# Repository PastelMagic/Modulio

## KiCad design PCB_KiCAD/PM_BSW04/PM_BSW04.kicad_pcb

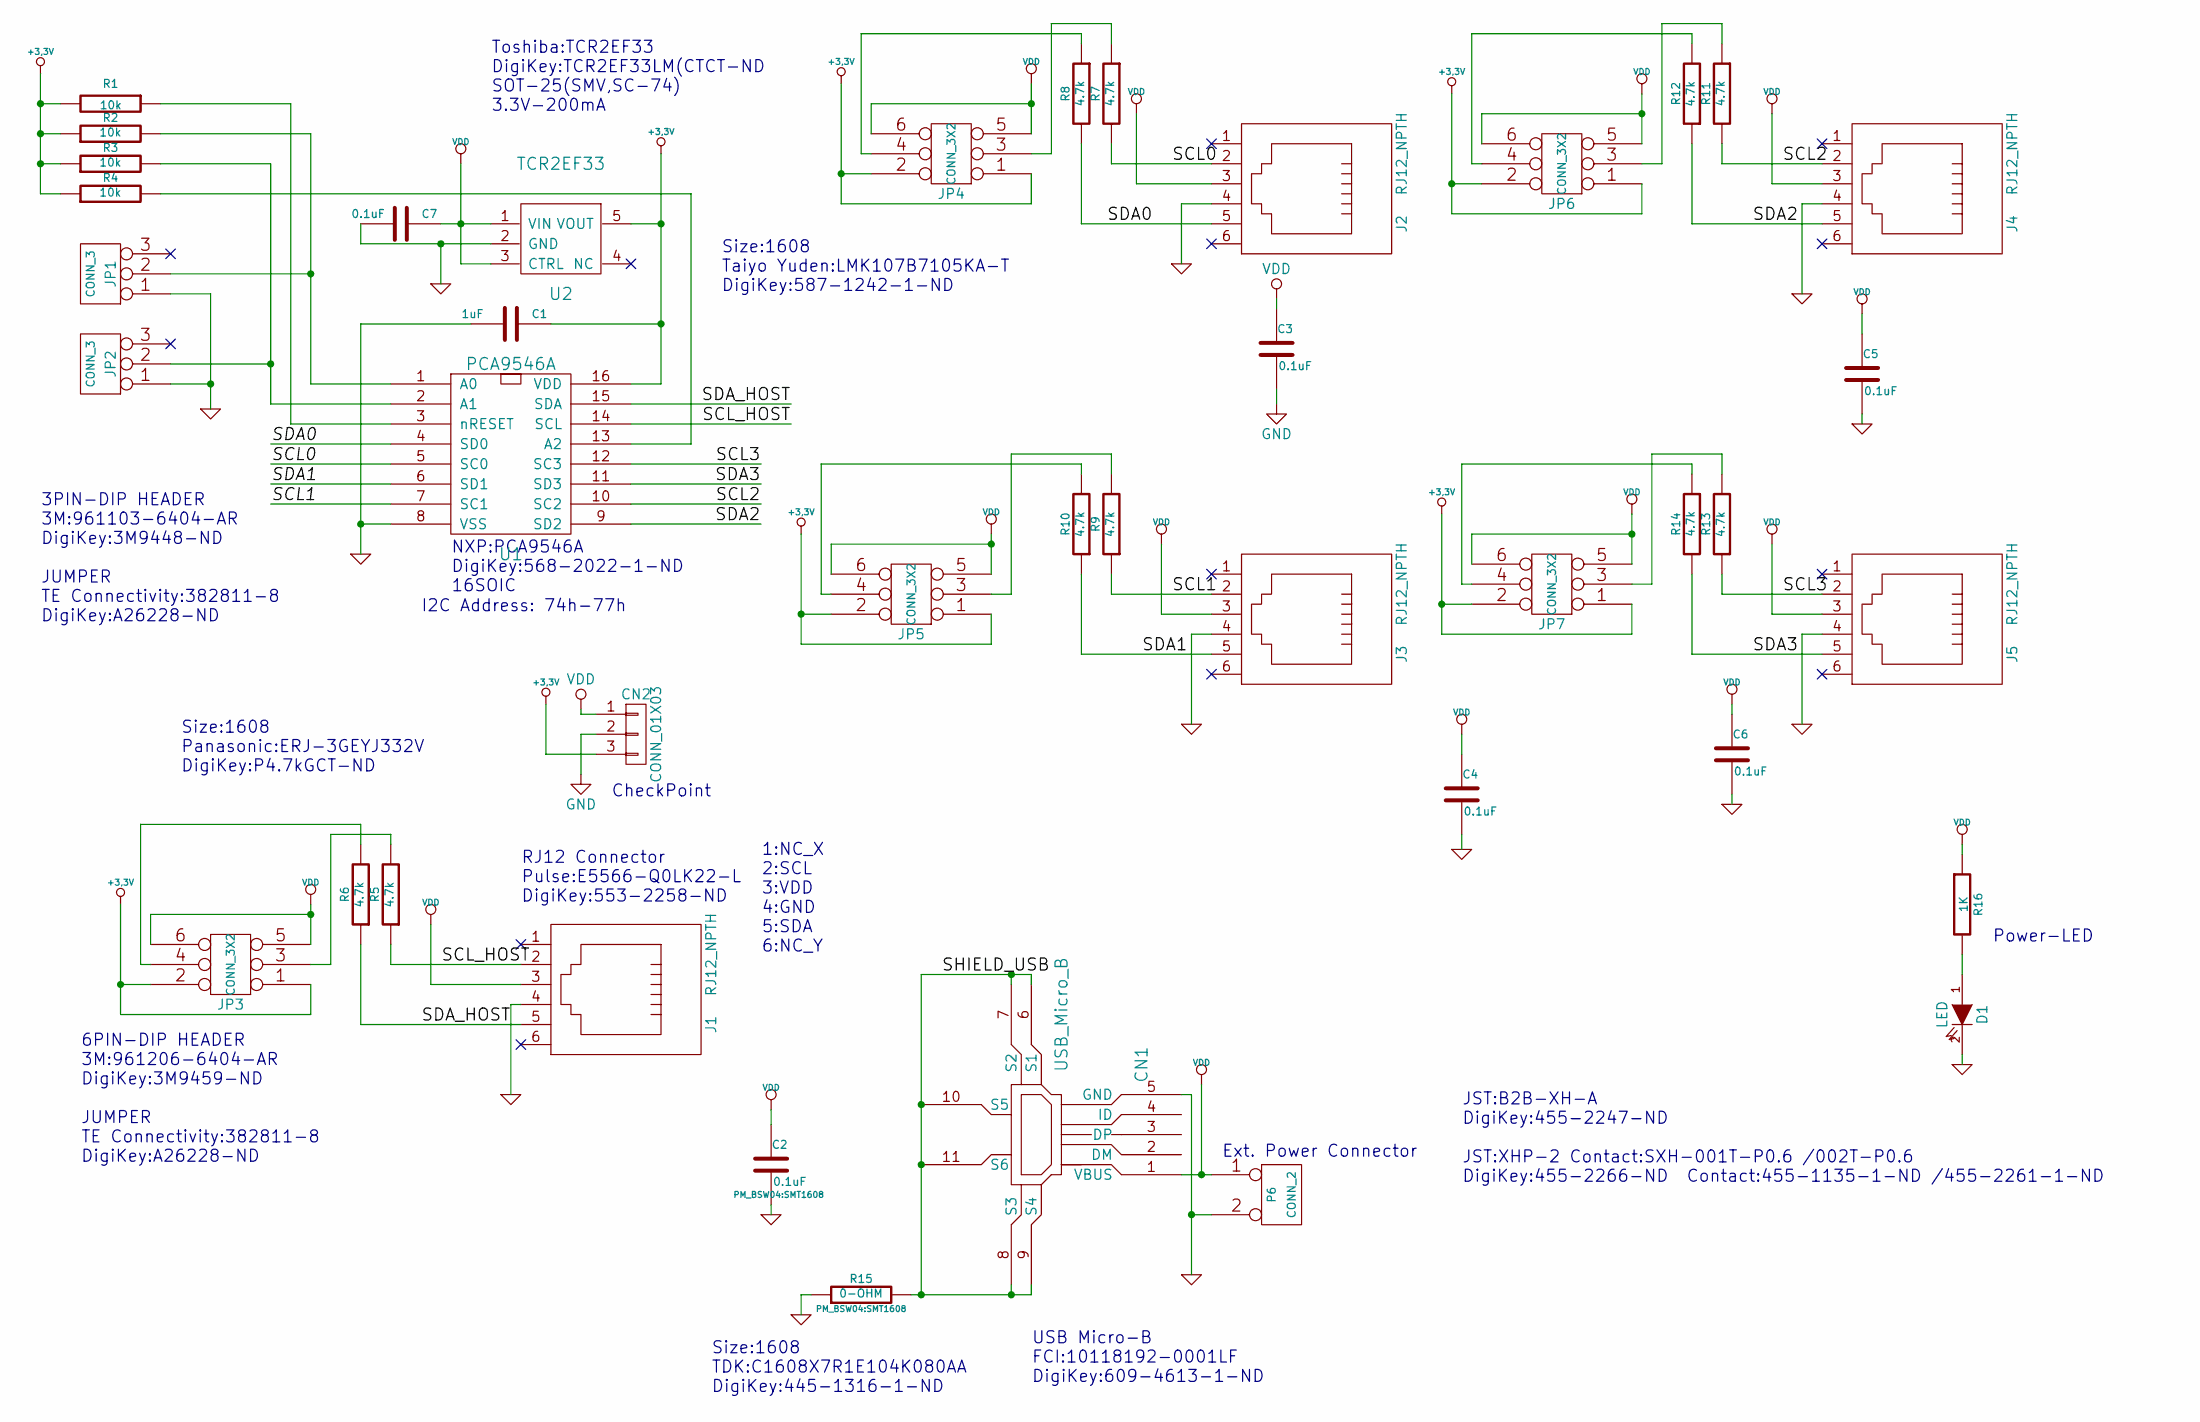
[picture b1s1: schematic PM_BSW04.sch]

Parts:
C1: 1uF; SMT1608
C2, C3, C4, C5, C6, C7: 0.1uF; SMT1608
CN1: USB_Micro_B; FCI_MicroB
CN2: CONN_01X03; 3DIP100E
D1: LED; LED_SMT1608
J1, J2, J3, J4, J5: RJ12_NPTH; RJ12_E5566-Q0LK22-L
JP1, JP2: CONN_3; 3DIP100E
JP3, JP4, JP5, JP6, JP7: CONN_3X2; 6DIP100E
P6: CONN_2; CN_B2B_XH_AM
R1, R2, R3, R4: 10k; SMT1608
R5, R6, R7, R8, R9, R10, R11, R12, R13, R14: 4.7k; SMT1608
R15: 0-OHM; SMT1608
R16: 1K; SMT1608
U1: PCA9546A; SO16_SOT109
U2: TCR2EF33; SMV2915

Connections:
+3.3V: C1.1, CN2.3, JP3.1, JP3.2, JP4.1, JP4.2, JP5.1, JP5.2, JP6.1, JP6.2, JP7.1, JP7.2, R1.2, R2.1, R3.1, R4.1, U1.16 (VDD), U2.5 (VOUT)
/SCL0: J2.2, R7.2, U1.5 (SC0)
/SCL1: J3.2, R9.1, U1.7 (SC1)
/SCL2: J4.2, R11.2, U1.10 (SC2)
/SCL3: J5.2, R13.1, U1.12 (SC3)
/SCL_HOST: J1.2, R5.1, U1.14 (SCL)
/SDA0: J2.5, R8.2, U1.4 (SD0)
/SDA1: J3.5, R10.1, U1.6 (SD1)
/SDA2: J4.5, R12.1, U1.9 (SD2)
/SDA3: J5.5, R14.2, U1.11 (SD3)
/SDA_HOST: J1.5, R6.1, U1.15 (SDA)
/SHIELD_USB: CN1.6 (S1), CN1.7 (S2), CN1.8 (S3), CN1.9 (S4), CN1.10 (S5), CN1.11 (S6), R15.2
GND: C1.2, C2.2, C3.2, C4.2, C5.2, C6.2, C7.2, CN1.5 (GND), CN2.2, D1.2 (K), J1.4, J2.4, J3.4, J4.4, J5.4, JP1.1, JP2.1, P6.2 (PM), R15.1, U1.8 (VSS), U2.2 (GND)
unnamed: D1.1 (A), R16.2
unnamed: JP1.2 (PM), R2.2, U1.1 (A0)
unnamed: JP2.2 (PM), R3.2, U1.2 (A1)
unnamed: JP3.3, R5.2
unnamed: JP3.4, R6.2
unnamed: JP4.3, R7.1
unnamed: JP4.4, R8.1
unnamed: JP5.3, R9.2
unnamed: JP5.4, R10.2
unnamed: JP6.3, R11.1
unnamed: JP6.4, R12.2
unnamed: JP7.3, R13.2
unnamed: JP7.4, R14.1
unnamed: R1.1, U1.3 (nRESET)
unnamed: R4.2, U1.13 (A2)
VDD: C2.1, C3.1, C4.1, C5.1, C6.1, C7.1, CN1.1 (VBUS), CN2.1, J1.3, J2.3, J3.3, J4.3, J5.3, JP3.5, JP3.6, JP4.5, JP4.6, JP5.5, JP5.6, JP6.5, JP6.6, JP7.5, JP7.6, P6.1, R16.1, U2.1 (VIN), U2.3 (CTRL)

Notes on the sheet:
1:NC_X 2:SCL 3:VDD 4:GND 5:SDA 6:NC_Y
6PIN-DIP HEADER 3M:961206-6404-AR DigiKey:3M9459-ND JUMPER TE Connectivity:382811-8 DigiKey:A26228-ND
NXP:PCA9546A DigiKey:568-2022-1-ND 16SOIC
I2C Address: 74h-77h
RJ12 Connector Pulse:E5566-Q0LK22-L DigiKey:553-2258-ND
Size:1608 Panasonic:ERJ-3GEYJ332V DigiKey:P4.7kGCT-ND
Size:1608 TDK:C1608X7R1E104K080AA DigiKey:445-1316-1-ND
USB Micro-B FCI:10118192-0001LF DigiKey:609-4613-1-ND
3PIN-DIP HEADER 3M:961103-6404-AR DigiKey:3M9448-ND JUMPER TE Connectivity:382811-8 DigiKey:A26228-ND
Toshiba:TCR2EF33 DigiKey:TCR2EF33LM(CTCT-ND SOT-25(SMV,SC-74) 3.3V-200mA
Size:1608 Taiyo Yuden:LMK107B7105KA-T DigiKey:587-1242-1-ND
Power-LED
JST:B2B-XH-A DigiKey:455-2247-ND JST:XHP-2 Contact:SXH-001T-P0.6 /002T-P0.6 DigiKey:455-2266-ND Contact:455-1135-1-ND /455-2261-1-ND
CheckPoint
Ext. Power Connector

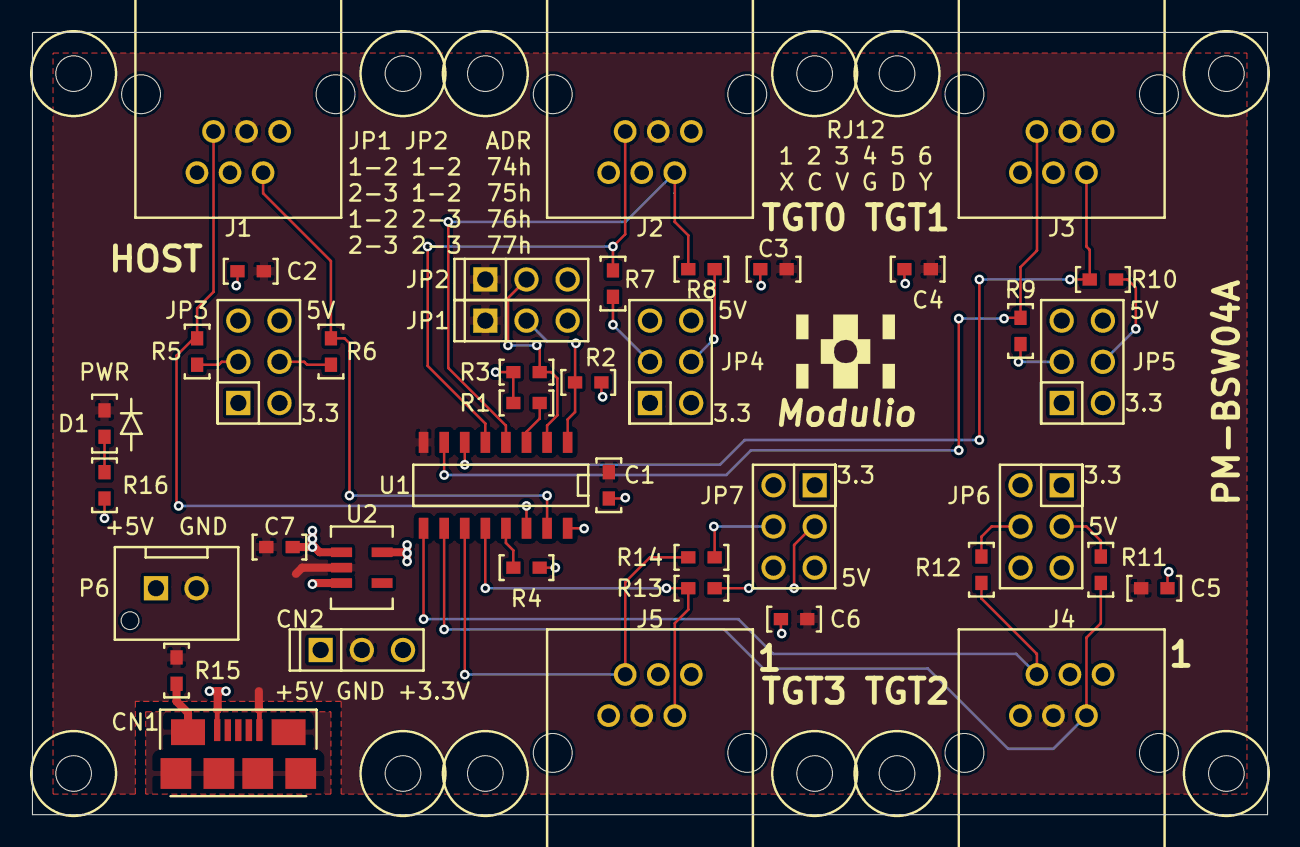
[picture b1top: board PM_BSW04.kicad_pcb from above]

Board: 2 copper layers, 76.2 x 48.3 mm, 53 parts (0 on the bottom side), 29 nets.

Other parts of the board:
HOLE2_2MM_01, HOLE2_2MM_02, HOLE2_2MM_03, HOLE2_2MM_04, HOLE2_2MM_05, HOLE2_2MM_06, HOLE2_2MM_07, HOLE2_2MM_08, HOLE2_2MM_09, HOLE2_2MM_10, HOLE2_2MM_11, HOLE2_2MM_12: VAL**; HOLE2_2MM

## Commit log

2022-03-14 Set theme jekyll-theme-slate
